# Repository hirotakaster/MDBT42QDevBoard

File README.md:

# MDBT42QDevBoard
MDB42 Eagle library can download from <a href="http://www.raytac.com/download/MDBT42/MDBT42Q_MDBT42Q-P%20Footprint_Design%20Guide-20170503.zip">here</a>.

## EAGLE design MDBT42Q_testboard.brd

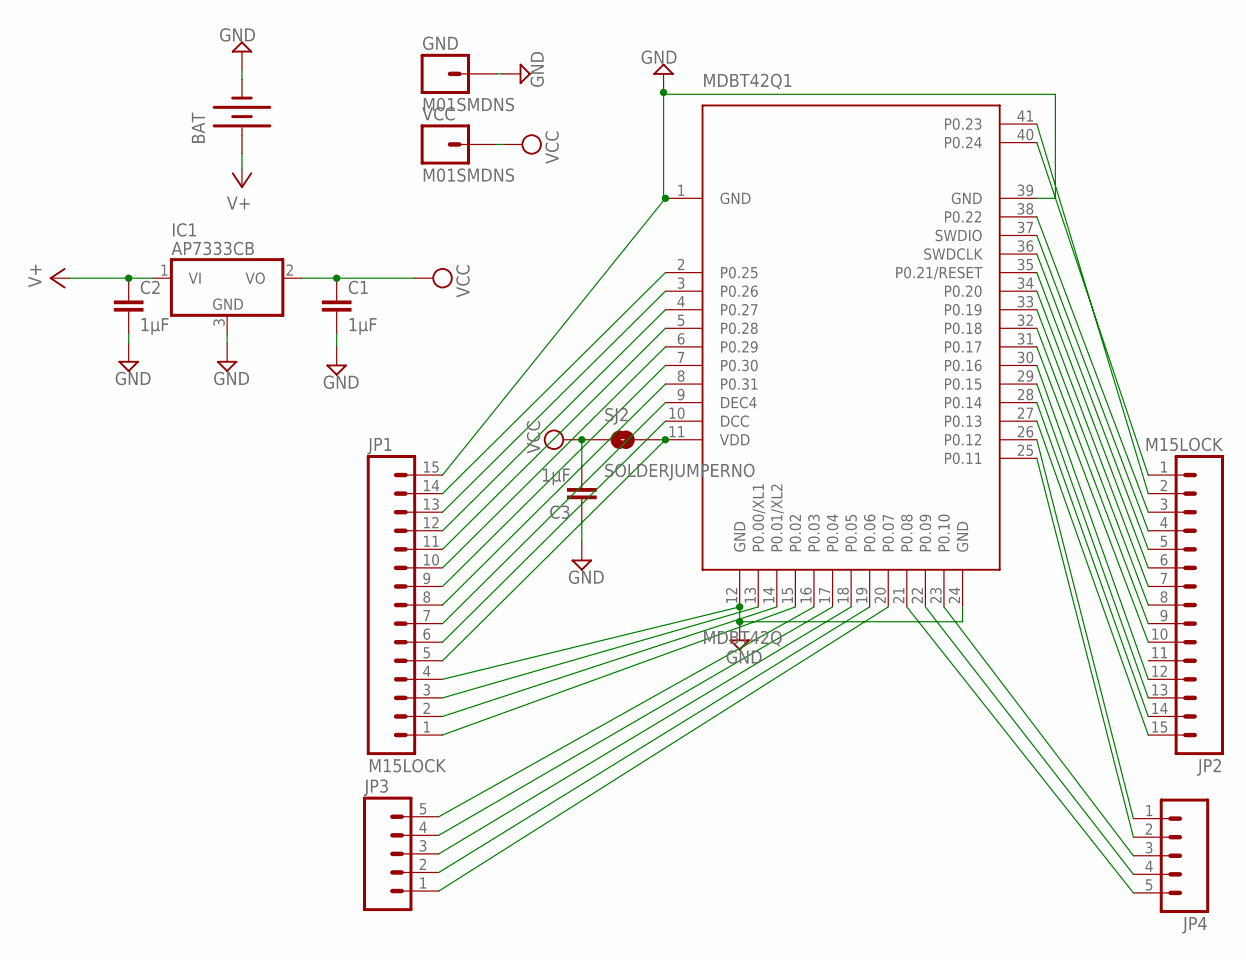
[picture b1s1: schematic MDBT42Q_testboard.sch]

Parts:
BAT: BATTERYFOB; BATTERY_20MM_PTH_COMPACT
C1, C2, C3: 1μF; 0603-CAP
GND: M01SMDNS; 1X01NS
IC1: AP7333CB; SOT23
JP1, JP2: M15LOCK; 1X15_LOCK
JP3, JP4: M05LOCK; 1X05_LOCK
MDBT42Q1: MDBT42Q
SJ2: SOLDERJUMPERNO; SJ_2S-NO
VCC: M01SMDNS; 1X01NS

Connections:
GND: BAT.2 (-), C1.2, C2.2, C3.1, GND.1, IC1.3 (GND), JP1.4, JP1.15, MDBT42Q1.1 (GND), MDBT42Q1.12 (GND), MDBT42Q1.24 (GND), MDBT42Q1.39 (GND)
unnamed: JP1.5, MDBT42Q1.11 (VDD), SJ2.2
unnamed: JP1.14, MDBT42Q1.2 (P0.25)
unnamed: JP1.13, MDBT42Q1.3 (P0.26)
unnamed: JP1.12, MDBT42Q1.4 (P0.27)
unnamed: JP1.11, MDBT42Q1.5 (P0.28)
unnamed: JP2.9, MDBT42Q1.32 (P0.18)
unnamed: JP1.10, MDBT42Q1.6 (P0.29)
unnamed: JP1.9, MDBT42Q1.7 (P0.30)
unnamed: JP1.8, MDBT42Q1.8 (P0.31)
unnamed: JP1.7, MDBT42Q1.9 (DEC4)
unnamed: JP1.6, MDBT42Q1.10 (DCC)
unnamed: JP1.3, MDBT42Q1.13 (P0.00/XL1)
unnamed: JP1.2, MDBT42Q1.14 (P0.01/XL2)
unnamed: JP1.1, MDBT42Q1.15 (P0.02)
unnamed: JP3.5, MDBT42Q1.16 (P0.03)
unnamed: JP3.4, MDBT42Q1.17 (P0.04)
unnamed: JP3.3, MDBT42Q1.18 (P0.05)
unnamed: JP3.2, MDBT42Q1.19 (P0.06)
unnamed: JP3.1, MDBT42Q1.20 (P0.07)
unnamed: JP4.5, MDBT42Q1.21 (P0.08)
unnamed: JP4.4, MDBT42Q1.22 (P0.09)
unnamed: JP4.3, MDBT42Q1.23 (P0.10)
unnamed: JP4.2, MDBT42Q1.25 (P0.11)
unnamed: JP4.1, MDBT42Q1.26 (P0.12)
unnamed: JP2.15, MDBT42Q1.27 (P0.13)
unnamed: JP2.14, MDBT42Q1.28 (P0.14)
unnamed: JP2.13, MDBT42Q1.29 (P0.15)
unnamed: JP2.12, MDBT42Q1.30 (P0.16)
unnamed: JP2.10, MDBT42Q1.31 (P0.17)
unnamed: JP2.8, MDBT42Q1.33 (P0.19)
unnamed: JP2.7, MDBT42Q1.34 (P0.20)
unnamed: JP2.6, MDBT42Q1.35 (P0.21/RESET)
unnamed: JP2.5, MDBT42Q1.36 (SWDCLK)
unnamed: JP2.4, MDBT42Q1.37 (SWDIO)
unnamed: JP2.3, MDBT42Q1.38 (P0.22)
unnamed: JP2.1, MDBT42Q1.40 (P0.24)
unnamed: JP2.2, MDBT42Q1.41 (P0.23)
V+: BAT.1 (+), C2.1, IC1.1 (VI)
VCC: C1.1, C3.2, IC1.2 (VO), SJ2.1, VCC.1

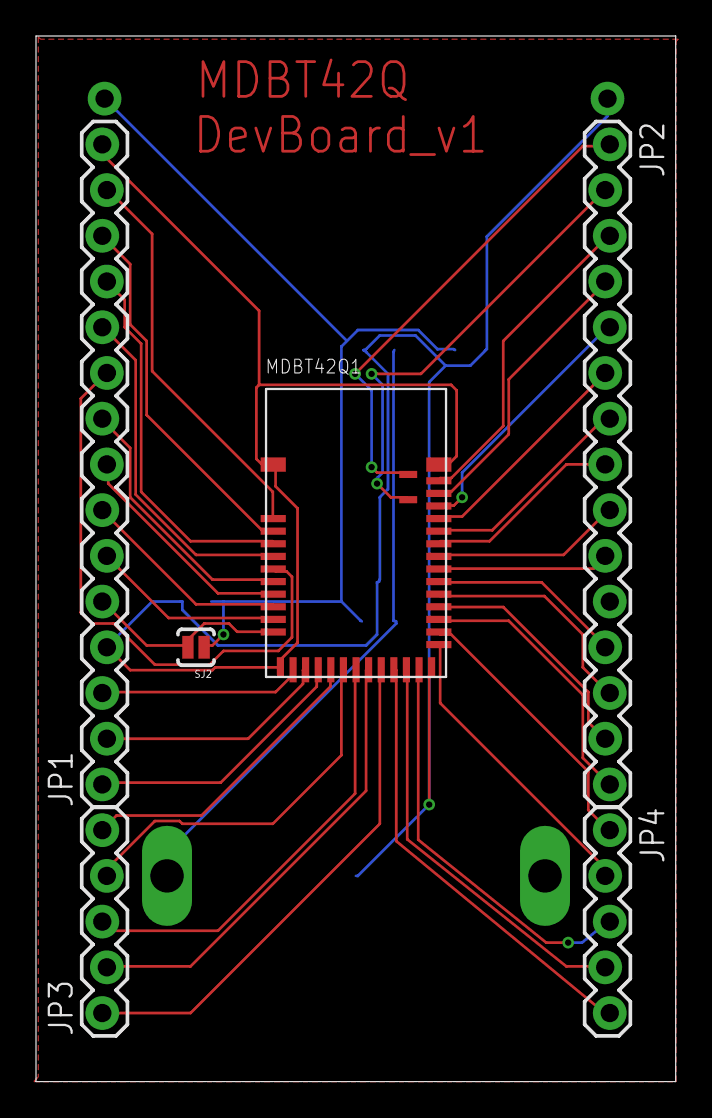
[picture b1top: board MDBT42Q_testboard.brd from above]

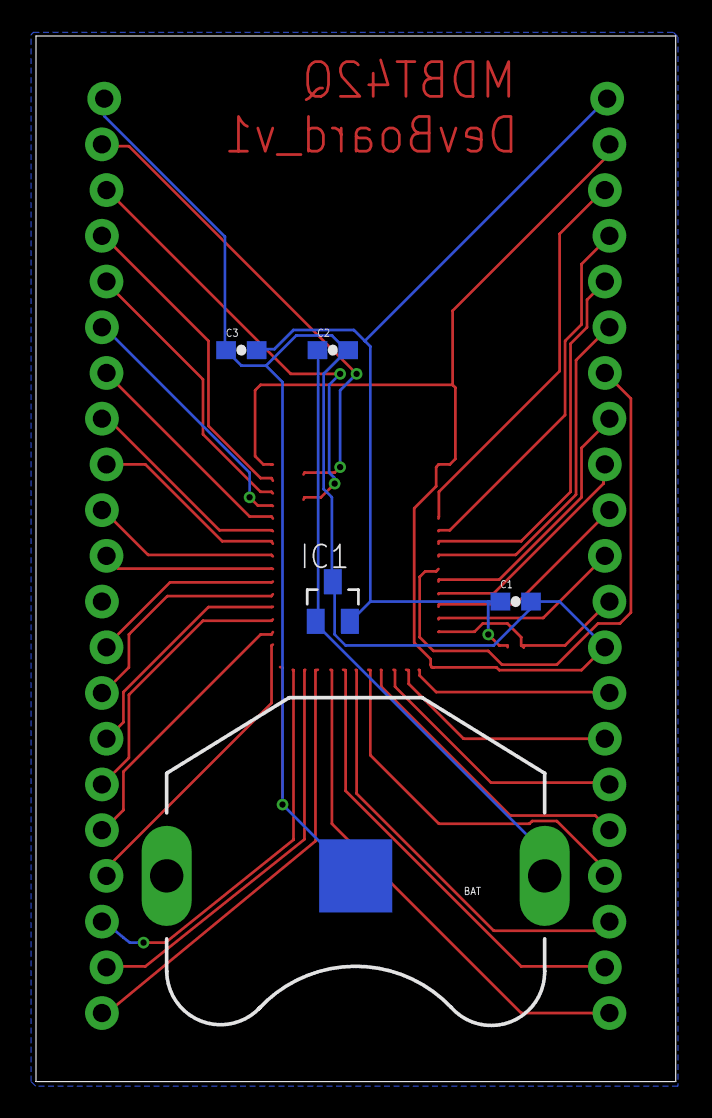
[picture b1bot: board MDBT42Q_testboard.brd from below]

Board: 2 copper layers, 35.5 x 58.1 mm, 13 parts (5 on the bottom side), 40 nets.

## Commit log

2017-07-11 update.

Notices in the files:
parts and their libraries:
SparkFun: Licensing: CC v3.0 Share-Alike You are welcome to use this library for commercial purposes.
